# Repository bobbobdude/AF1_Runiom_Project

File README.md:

# What this repo is about

I'm thinking that this repo can be a collection of everything we are up to with code, PCB design, 3D models and also general planning. Once we have a more substantial project we can reorganise the repo a little - but for now I'm chucking everything up there.

# What's with the name?

AF1 - Alla får en

Runiom - **Ru**ben, **Ni**ls and T**om**

Cute ey?

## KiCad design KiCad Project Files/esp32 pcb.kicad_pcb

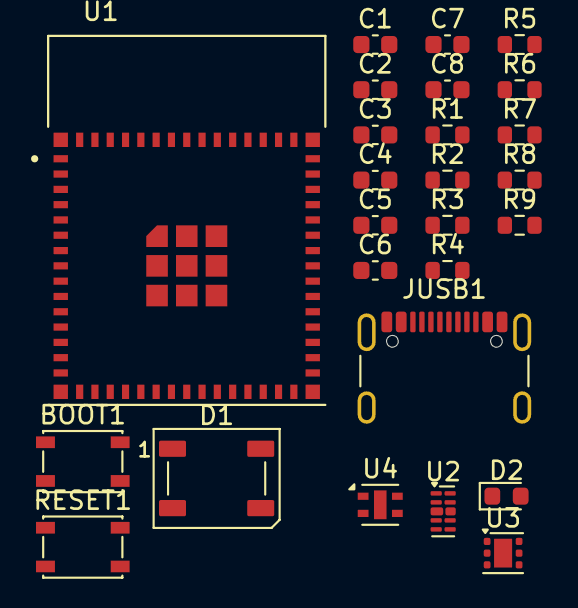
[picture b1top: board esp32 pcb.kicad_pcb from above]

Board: 2 copper layers, 26 parts (0 on the bottom side), 14 nets, no tracks yet.

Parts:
BOOT1: SW_SPST_PTS810
C1: C_Small; C_0603_1608Metric
C2, C4, C5, C8: 0.1uF; C_0603_1608Metric
C3, C6, C7: 10uF; C_0603_1608Metric
D1: WS2812B; LED_WS2812B_PLCC4_5.0x5.0mm_P3.2mm
D2: LED; D_0603_1608Metric
JUSB1: USB_C_Receptacle_USB2.0_16P; USB_C_Receptacle_GCT_USB4105-xx-A_16P_TopMnt_Horizontal
R1: R_Small; R_0603_1608Metric
R2, R3, R9: 5.1k; R_0603_1608Metric
R4, R5, R6: 10k; R_0603_1608Metric
R7: 1M; R_0603_1608Metric
R8: 200k; R_0603_1608Metric
RESET1: SW_SPST_PTS810
U1: ESP32-S3-MINI-1-N8; XCVR_ESP32-S3-MINI-1-N8
U2: D3V3XA4B10LP; Diodes_UDFN-10_1x2.5mm_P0.5mm
U3: TLV75801PDRV; WSON-6-1EP_2x2mm_P0.65mm_EP1x1.6mm
U4: ENS210; AMS_QFN-4-1EP_2x2mm_P0.95mm_EP0.7x1.6mm

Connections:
/3V3: C5.1, C7.1, D1.1 (VDD), R4.1, R5.1, R6.1, R7.1, R9.1, U3.1 (OUT), U4.1 (VDD)
/5VUSB: C6.1, JUSB1.A4 (VBUS), JUSB1.A9 (VBUS), JUSB1.B4 (VBUS), JUSB1.B9 (VBUS), U2.4, U3.4 (EN), U3.6 (IN)
/ESP32_EN: C4.1, R4.2, U1.45 (EN)
/GPIO0: C8.1, U1.4 (IO0)
/I2C_SCL: R6.2, U1.21 (IO17), U4.2 (SCL)
/I2C_SDA: R5.2, U1.22 (IO18), U4.3 (SDA)
/USB_N: JUSB1.A7 (D-), JUSB1.B7 (D-), U2.2
/USB_P: JUSB1.A6 (D+), JUSB1.B6 (D+), U2.1
GND: BOOT1.1, BOOT1.2, C2.2, C3.2, C4.2, C5.2, C6.2, C7.2, C8.2, D1.3 (VSS), D2.1 (K), JUSB1.A1 (GND), JUSB1.A12 (GND), JUSB1.B1 (GND), JUSB1.B12 (GND), JUSB1.SH (SHIELD), R2.2, R3.2, R8.2, RESET1.1, RESET1.2, U1.1 (GND), U1.2 (GND), U1.42 (GND), U1.43 (GND), U1.46 (GND), U1.47 (GND), U1.48 (GND), U1.49 (GND), U1.50 (GND), U1.51 (GND), U1.52 (GND), U1.53 (GND), U1.54 (GND), U1.55 (GND), U1.56 (GND), U1.57 (GND), U1.58 (GND), U1.59 (GND), U1.60 (GND), U1.61 (GND), U1.61_1 (GND), U1.61_2 (GND), U1.61_3 (GND), U1.61_4 (GND), U1.61_5 (GND), U1.61_6 (GND), U1.61_7 (GND), U1.61_8 (GND), U1.62 (GND), U1.63 (GND), U1.64 (GND), U1.65 (GND), U2.3 (VSS), U2.8 (VSS), U3.3 (GND), U3.7 (GND), U4.4 (GND), U4.5 (GND)
unnamed: D2.2 (A), R9.2
unnamed: JUSB1.A5 (CC1), R2.1
unnamed: JUSB1.B5 (CC2), R3.1
unnamed: C2.1, C3.1, U1.3 (3V3)
unnamed: R7.2, R8.1, U3.2 (FB)
